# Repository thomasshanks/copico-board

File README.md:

# CoPiCo PCB KiCad Files

The CoPiCo is a cartridge for the Tandy Color Computer that adds WiFi to and
serves as a boot ROM for the system. It is based on the Raspberry Pi Pico W
microcontroller dev board, which includes onboard WiFi.

[copico_rev0.1_schematic_v0.1.9.pdf](https://github.com/thomasshanks/copico-board/files/14322771/copico_rev0.1_schematic_v0.1.9.pdf)

## WiFi Connectivity

The firmware (see 'copico-firmware' repo) will behave more like a SPI WiFi
module or the WizNet chip (or perhaps both, depending on mode). It will, of
course, also allow listing and connecting to the desired WiFi network.

## ROM Emulation

CoPiCo will also support boot ROM emulation (initially just for a 1 KB ROM due
to limitations of first revision of the CoPiCo PCB). Henry Strickland
(@strickyak) plans to use this feature to load a version of his
"axiom" network boot ROM (see
https://github.com/strickyak/frobio/tree/main/frob3/booting).

## Other Future Capabilities

Future capabilities for the CoPiCo may include:
- VGA or HDMI output based on the captured contents of video RAM
- Logic capture / bus trace
- Remote debug, with breakpoints and watchpoints

## Stay Tuned to This Channel

Please star this repo and/or watch this space for updates as development
continues!

Thank you for being a part of the Retrocomputing community!

Thomas Shanks (copico@tshanks.org)    
13 Feb 2024

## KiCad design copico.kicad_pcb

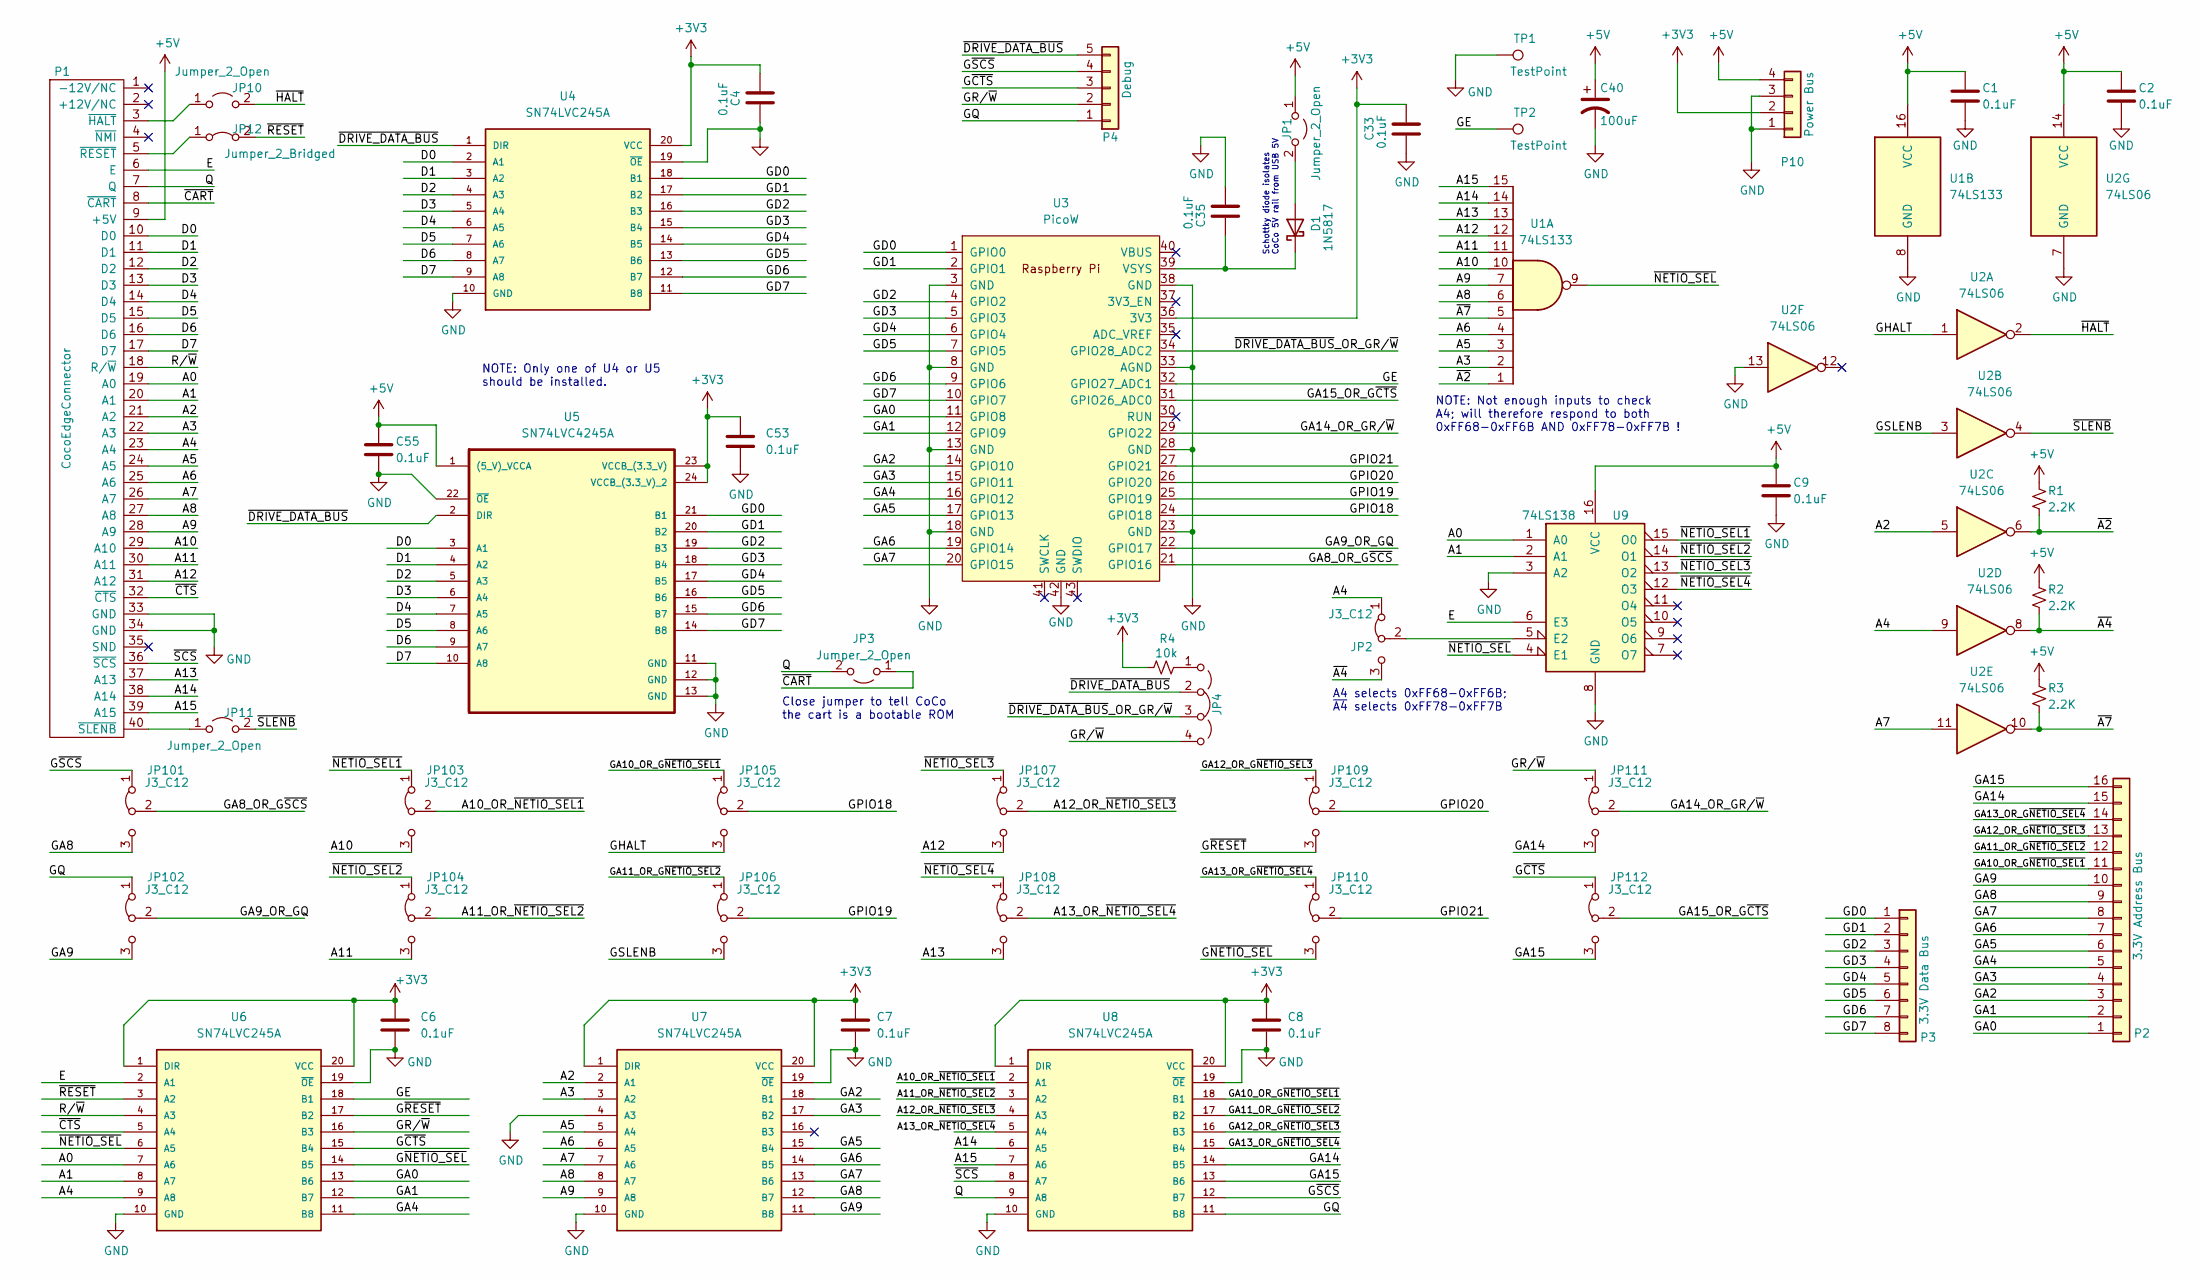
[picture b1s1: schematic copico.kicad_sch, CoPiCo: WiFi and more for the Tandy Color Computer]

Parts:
C1, C2, C4, C6, C7, C8, C9, C33, C35, C53, C55: 0.1uF; C_Disc_D5.0mm_W2.5mm_P5.00mm
C40: 100uF; CP_Radial_D7.5mm_P2.50mm
D1: 1N5817; D_DO-41_SOD81_P10.16mm_Horizontal
JP1, JP3, JP10, JP11: Jumper_2_Open; PinHeader_1x02_P2.54mm_Vertical
JP2, JP101, JP102, JP103, JP104, JP105, JP106, JP107, JP108, JP109, JP110, JP111, JP112: J3_C12; PinHeader_1x03_P2.54mm_Vertical
JP4: jp_ser_4pin_23cl; PinHeader_1x04_P2.54mm_Vertical
JP12: Jumper_2_Bridged; PinHeader_1x02_P2.54mm_Vertical
P1: CocoEdgeConnector; CocoCardEdge
P2: 3.3V Address Bus; PinHeader_1x16_P2.54mm_Vertical
P3: 3.3V Data Bus; PinHeader_1x08_P2.54mm_Vertical
P4: Debug; PinHeader_1x05_P2.54mm_Vertical
P10: Power Bus; PinHeader_1x04_P2.54mm_Vertical
R1, R2, R3: 2.2K; R_Axial_DIN0207_L6.3mm_D2.5mm_P10.16mm_Horizontal
R4: 10k; R_Axial_DIN0207_L6.3mm_D2.5mm_P10.16mm_Horizontal
TP1, TP2: TestPoint; PinHeader_1x01_P2.54mm_Vertical
U1: 74LS133; DIP-16_W7.62mm_LongPads
U2: 74LS06; DIP-14_W7.62mm_LongPads
U3: PicoW; RPi_PicoW_SMD_TH
U4, U6, U7, U8: SN74LVC245A; DIP20-2.54-26.2X7.62MM; MPN SN74LVC245AN
U5: SN74LVC4245A; SOIC-24W_7.5x15.4mm_P1.27mm
U9: 74LS138; DIP-16_W7.62mm_LongPads

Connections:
+3V3: C4.2, C6.1, C7.1, C8.1, C33.1, C53.1, P10.2, R4.1, U3.36 (3V3), U4.20 (VCC), U5.23 (VCCB_(3.3_V)), U5.24 (VCCB_(3.3_V)_2), U6.1 (DIR), U6.20 (VCC), U7.1 (DIR), U7.20 (VCC), U8.1 (DIR), U8.20 (VCC)
+5V: C1.1, C2.1, C9.1, C40.1, C55.1, JP1.1 (A), P1.9 (+5V), P10.4, R1.1, R2.1, R3.1, U1.16 (VCC), U2.14 (VCC), U5.1 ((5_V)_VCCA), U9.16 (VCC)
/A0: P1.19 (A0), U6.7 (A6), U9.1 (A0)
/A1: P1.20 (A1), U6.8 (A7), U9.2 (A1)
/A2: P1.21 (A2), U2.5, U7.2 (A1)
/A3: P1.22 (A3), U1.2, U7.3 (A2)
/A4: JP2.1 (A), P1.23 (A4), U2.9, U6.9 (A8)
/A5: P1.24 (A5), U1.3, U7.5 (A4)
/A6: P1.25 (A6), U1.4, U7.6 (A5)
/A7: P1.26 (A7), U2.11, U7.7 (A6)
/A8: P1.27 (A8), U1.6, U7.8 (A7)
/A9: P1.28 (A9), U1.7, U7.9 (A8)
/A10: JP103.3 (B), P1.29 (A10), U1.10
/A10_OR_~NETIO_SEL1: JP103.2 (C), U8.2 (A1)
/A11: JP104.3 (B), P1.30 (A11), U1.11
/A11_OR_~NETIO_SEL2: JP104.2 (C), U8.3 (A2)
/A12: JP107.3 (B), P1.31 (A12), U1.12
/A12_OR_~NETIO_SEL3: JP107.2 (C), U8.4 (A3)
/A13: JP108.3 (B), P1.37 (A13), U1.13
/A13_OR_~NETIO_SEL4: JP108.2 (C)
/A14: P1.38 (A14), U1.14, U8.6 (A5)
/A15: P1.39 (A15), U1.15, U8.7 (A6)
/D0: P1.10 (D0), U4.2 (A1), U5.3 (A1)
/D1: P1.11 (D1), U4.3 (A2), U5.4 (A2)
/D2: P1.12 (D2), U4.4 (A3), U5.5 (A3)
/D3: P1.13 (D3), U4.5 (A4), U5.6 (A4)
/D4: P1.14 (D4), U4.6 (A5), U5.7 (A5)
/D5: P1.15 (D5), U4.7 (A6), U5.8 (A6)
/D6: P1.16 (D6), U4.8 (A7), U5.9 (A7)
/D7: P1.17 (D7), U4.9 (A8), U5.10 (A8)
/E: P1.6 (E), U6.2 (A1), U9.6 (E3)
/GA0: P2.1, U3.11 (GPIO8), U6.13 (B6)
/GA1: P2.2, U3.12 (GPIO9), U6.12 (B7)
/GA2: P2.3, U3.14 (GPIO10), U7.18 (B1)
/GA3: P2.4, U3.15 (GPIO11), U7.17 (B2)
/GA4: P2.5, U3.16 (GPIO12), U6.11 (B8)
/GA5: P2.6, U3.17 (GPIO13), U7.15 (B4)
/GA6: P2.7, U3.19 (GPIO14), U7.14 (B5)
/GA7: P2.8, U3.20 (GPIO15), U7.13 (B6)
/GA8: JP101.3 (B), P2.9, U7.12 (B7)
/GA8_OR_G~SCS: JP101.2 (C), U3.21 (GPIO16)
/GA9: JP102.3 (B), P2.10, U7.11 (B8)
/GA9_OR_GQ: JP102.2 (C), U3.22 (GPIO17)
/GA10_OR_G~NETIO_SEL1: JP105.1 (A), P2.11, U8.18 (B1)
/GA11_OR_G~NETIO_SEL2: JP106.1 (A), P2.12, U8.17 (B2)
/GA12_OR_G~NETIO_SEL3: JP109.1 (A), P2.13, U8.16 (B3)
/GA13_OR_G~NETIO_SEL4: JP110.1 (A), P2.14, U8.15 (B4)
/GA14: JP111.3 (B), P2.15, U8.14 (B5)
/GA14_OR_GR/~W: JP111.2 (C), U3.29 (GPIO22)
/GA15: JP112.3 (B), P2.16, U8.13 (B6)
/GA15_OR_G~CTS: JP112.2 (C), U3.31 (GPIO26_ADC0)
/GD0: P3.1, U3.1 (GPIO0), U4.18 (B1), U5.21 (B1)
/GD1: P3.2, U3.2 (GPIO1), U4.17 (B2), U5.20 (B2)
/GD2: P3.3, U3.4 (GPIO2), U4.16 (B3), U5.19 (B3)
/GD3: P3.4, U3.5 (GPIO3), U4.15 (B4), U5.18 (B4)
/GD4: P3.5, U3.6 (GPIO4), U4.14 (B5), U5.17 (B5)
/GD5: P3.6, U3.7 (GPIO5), U4.13 (B6), U5.16 (B6)
/GD6: P3.7, U3.9 (GPIO6), U4.12 (B7), U5.15 (B7)
/GD7: P3.8, U3.10 (GPIO7), U4.11 (B8), U5.14 (B8)
/GE: TP2.1, U3.32 (GPIO27_ADC1), U6.18 (B1)
/GHALT: JP105.3 (B), U2.1
/GPIO18: JP105.2 (C), U3.24 (GPIO18)
/GPIO19: JP106.2 (C), U3.25 (GPIO19)
/GPIO20: JP109.2 (C), U3.26 (GPIO20)
/GPIO21: JP110.2 (C), U3.27 (GPIO21)
/GQ: JP102.1 (A), P4.1, U8.11 (B8)
/GR/~W: JP4.4 (D), JP111.1 (A), P4.2, U6.16 (B3)
/GSLENB: JP106.3 (B), U2.3
/G~CTS: JP112.1 (A), P4.3, U6.15 (B4)
/G~NETIO_SEL: JP110.3 (B), U6.14 (B5)
/G~RESET: JP109.3 (B), U6.17 (B2)
/G~SCS: JP101.1 (A), P4.4, U8.12 (B7)
/Q: JP3.2 (B), P1.7 (Q), U8.9 (A8)
/R/~W: P1.18 (R/~W), U6.4 (A3)
/~A2: R1.2, U1.1, U2.6
/~A4: JP2.3 (B), R2.2, U2.8
/~A7: R3.2, U1.5, U2.10
/~CART: JP3.1 (A), P1.8 (~CART)
/~CTS: P1.32 (~CTS), U6.5 (A4)
/~DRIVE_DATA_BUS: JP4.2 (B), P4.5, U4.1 (DIR), U5.2 (DIR)
/~DRIVE_DATA_BUS_OR_GR/~W: JP4.3 (C), U3.34 (GPIO28_ADC2)
/~HALT: JP10.2 (B), U2.2
/~NETIO_SEL1: JP103.1 (A), U9.15 (O0)
/~NETIO_SEL2: JP104.1 (A), U9.14 (O1)
/~NETIO_SEL3: JP107.1 (A), U9.13 (O2)
/~NETIO_SEL4: JP108.1 (A), U9.12 (O3)
/~NETIO_SEL: U1.9, U6.6 (A5), U9.4 (E1)
/~RESET: JP12.2 (B), U6.3 (A2)
/~SCS: P1.36 (~SCS), U8.8 (A7)
/~SLENB: JP11.2 (B), U2.4
GND: C1.2, C2.2, C4.1, C6.2, C7.2, C8.2, C9.2, C33.2, C35.2, C40.2, C53.2, C55.2, P1.33 (GND), P1.34 (GND), P10.1, P10.3, TP1.1, U1.8 (GND), U2.7 (GND), U2.13, U3.3 (GND), U3.8 (GND), U3.13 (GND), U3.18 (GND), U3.23 (GND), U3.28 (GND), U3.33 (AGND), U3.38 (GND), U3.42 (GND), U4.10 (GND), U4.19 (~OE), U5.11 (GND), U5.12 (GND), U5.13 (GND), U5.22 (~OE), U6.10 (GND), U6.19 (~OE), U7.4 (A3), U7.10 (GND), U7.19 (~OE), U8.10 (GND), U8.19 (~OE), U9.3 (A2), U9.8 (GND)
unnamed: D1.2 (A), JP1.2 (B)
unnamed: C35.1, D1.1 (K), U3.39 (VSYS)
unnamed: JP2.2 (C), U9.5 (E2)
unnamed: JP4.1 (A), R4.2
unnamed: JP10.1 (A), P1.3 (~HALT)
unnamed: JP11.1 (A), P1.40 (~SLENB)
unnamed: JP12.1 (A), P1.5 (~RESET)

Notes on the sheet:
NOTE: Not enough inputs to check A4; will therefore respond to both 0xFF68-0xFF6B AND 0xFF78-0xFF7B !
NOTE: Only one of U4 or U5 should be installed.
Schottky diode isolates CoCo 5V rail from USB 5V
A4 selects 0xFF68-0xFF6B; ~{A4} selects 0xFF78-0xFF7B
Close jumper to tell CoCo the cart is a bootable ROM

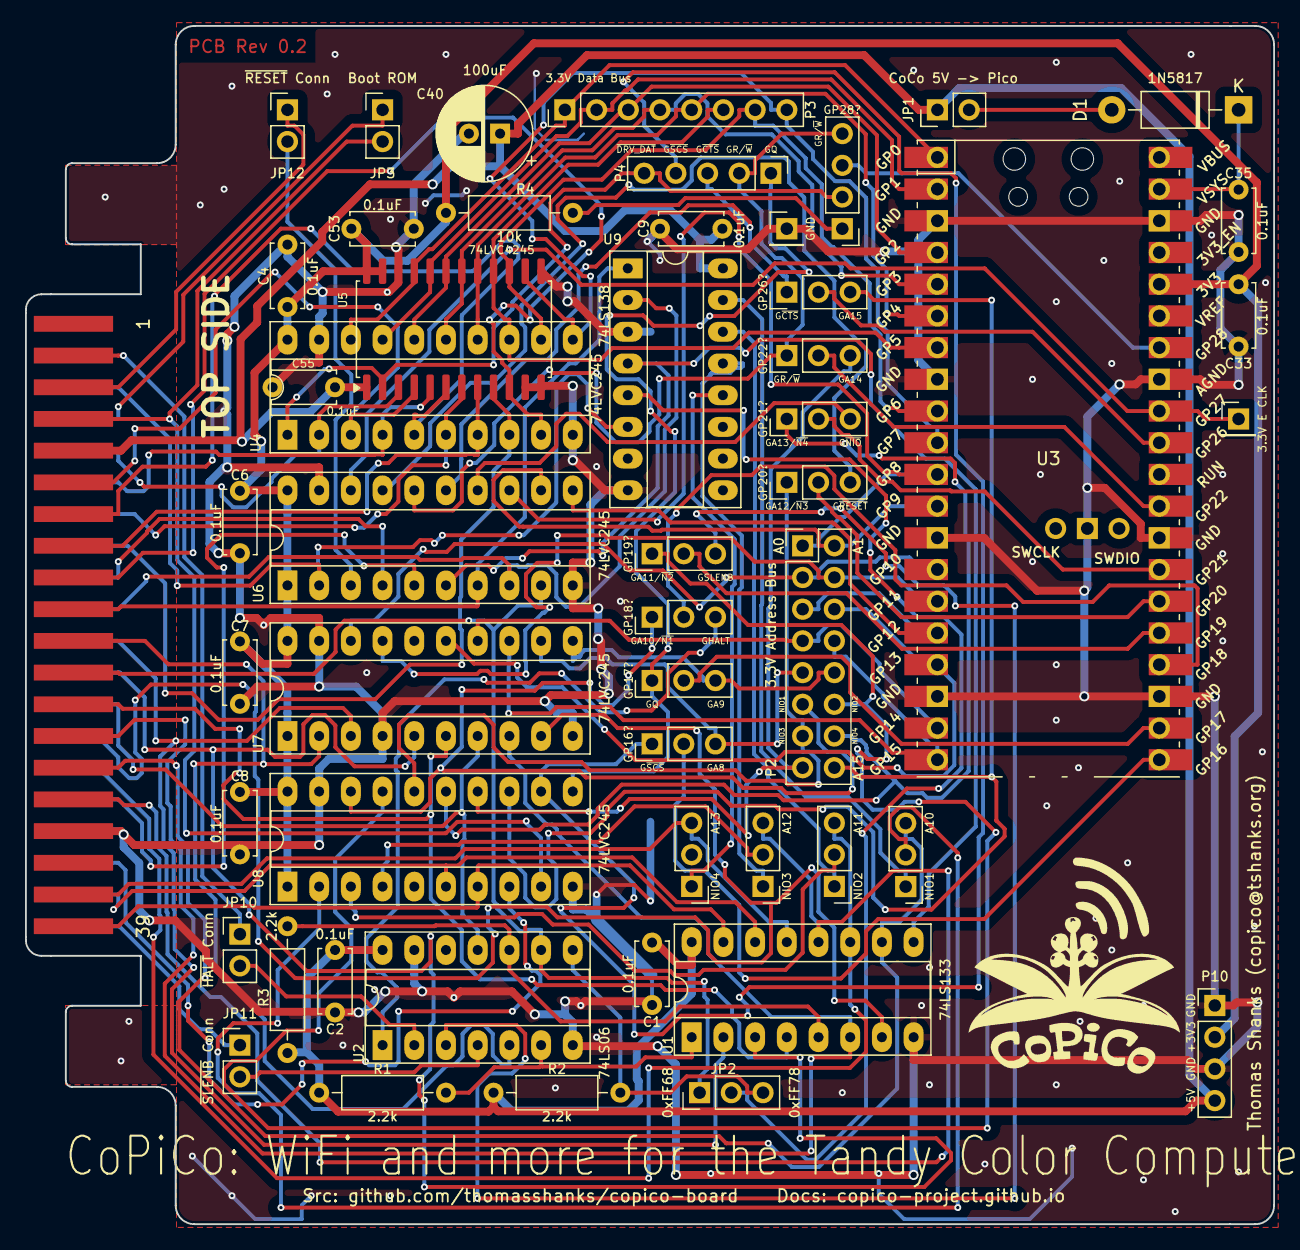
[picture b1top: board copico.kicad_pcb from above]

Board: 2 copper layers, 100.0 x 96.0 mm, 54 parts (0 on the bottom side), 97 nets.

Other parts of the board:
G0: LOGO; logo_small
G2: LOGO; logo_medium

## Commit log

2024-02-16 Initial commit of PCB Rev 0.1 as built
2024-02-18 Add PCB images to README.md
2024-02-18 Update README.md with schematic PNG and PDF
2024-02-18 Correct signal naming on schematic & URL on PCB
2024-03-20 Update component values to match reality
    - Update component values to match what we actually used on the board.
    - Add an additional decoupling capacitor for the PicoW to the schematic. This
    capacitor is not yet laid out onto the actual board.
    - Take the bar off of the GHALT and GSLENB signals since they are actually
    active high, not active low.
    - Additional schematic cleanup.
2024-03-26 Update silkscreen with component values
    I accidentally left the component value silkscreening off the first run of the
    board. Add these back, as well as adding some labels to the jumpers and such.
    Update PCB Rev in solder mask to 0.1a, but leave the copper layer PCB Rev at
    0.1 since that layer has not changed.
2024-04-02 Update Gerbers with those from Rev 0.1a PCBWay run
2024-04-10 Add handwritten Bill of Materials
2024-04-18 Update schematic to REV 2
    The REV 2 design:
    - allows the CoCo to power the PicoW via a Schottky diode, which prevents
    backfeeding one power supply from the other
    - moves the address decode for the NETIO feature out of the PicoW firmware into
    discrete 74LS logic in order to allow it to respond using only PIO and DMA
2024-04-19 FIXME: need pull-up R when DRIVE_DATA_BUS floating
    Add a FIXME that indicates the need for DRIVE_DATA_BUS to be pulled high when
    the GPIO28 jumper is set to send GR//W to the PicoW instead of getting
    DRIVE_DATA_BUS from the PicoW on that GPIO
2024-04-29 Update BOM_copico.csv for Rev 2 PCB
2024-04-29 Update PCB layout with Rev 0.2 schematic changes
2024-04-29 Assigned Nets, added pullup for drive_data_bus
    Assigned Netclasses for PWR, GND, and Addresses(3.3V only).
    Added pullup resistor to drive_data_bus when jumper changed to
    disconnected from pi
    Added 4pin series jumper with custom symbol to connect the
    pullup resistor.
2024-04-29 Changed some capacitors and labels
2024-05-01 Update README.md with Rev 0.2 PCB images/schematic
2024-05-12 Add copico logo to repo for README.md use
2024-05-12 Upload CoPiCo description slide for README.md use
2024-05-12 Rename copico__logo.png to copico_logo.png

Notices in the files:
copico.kicad_pcb:
Board footprint based on the Public Domain CoCoProtoBoard, which can be
Released under the MIT License (opensource.org/license/mit)
